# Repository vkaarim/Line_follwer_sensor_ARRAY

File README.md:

# 16-Channel IR Sensor Array PCB

> Personal hardware project for my robotics portfolio.

---

## Purpose

Design a custom 16-channel infrared sensor array PCB for future high-speed Line Follower robots.

This board will replace commercial sensor arrays and provide a platform for future improvements and experiments.

---

## Status

- [x] Schematic completed
- [x] PCB completed
- [x] 3D model verified
- [x] DRC passed
- [x] Gerber generated
- [x] Uploaded to GitHub

Version: **V1**

---

## Repository Structure

```
Hardware/
Images/
Manufacturing/
Backups/
README.md
```

---

## Images

### PCB Layout

### Schematic

### 3D Front

### 3D Back

---

## Main Specifications

- Software: KiCad
- Sensor Channels: 16
- PCB Type: 2 Layers
- Sensor Type: TCRT5000
- Target Robot: Line Follower

---

## Files Included

✔ KiCad Project

✔ Schematic

✔ PCB Layout

✔ Gerber Files

✔ 3D Images

✔ Backups

---

## Notes

Things I learned while designing this PCB:

- Organizing footprints before routing saves time.
- Keep signal routing clean and avoid unnecessary crossings.
- Always run DRC before generating Gerbers.
- Name files and folders consistently.
- Save manufacturing files separately from project files.

---

## Future Improvements

Version 2 ideas:

- Use SMD components where possible.
- Reduce PCB size.
- Improve sensor spacing.
- Add calibration LEDs.
- Add onboard multiplexer.
- Improve silkscreen readability.

---

## Manufacturing

Gerber files are available inside the repository.

---

## Author

Karim Rahou

National Higher School of Autonomous Systems

Personal learning project.

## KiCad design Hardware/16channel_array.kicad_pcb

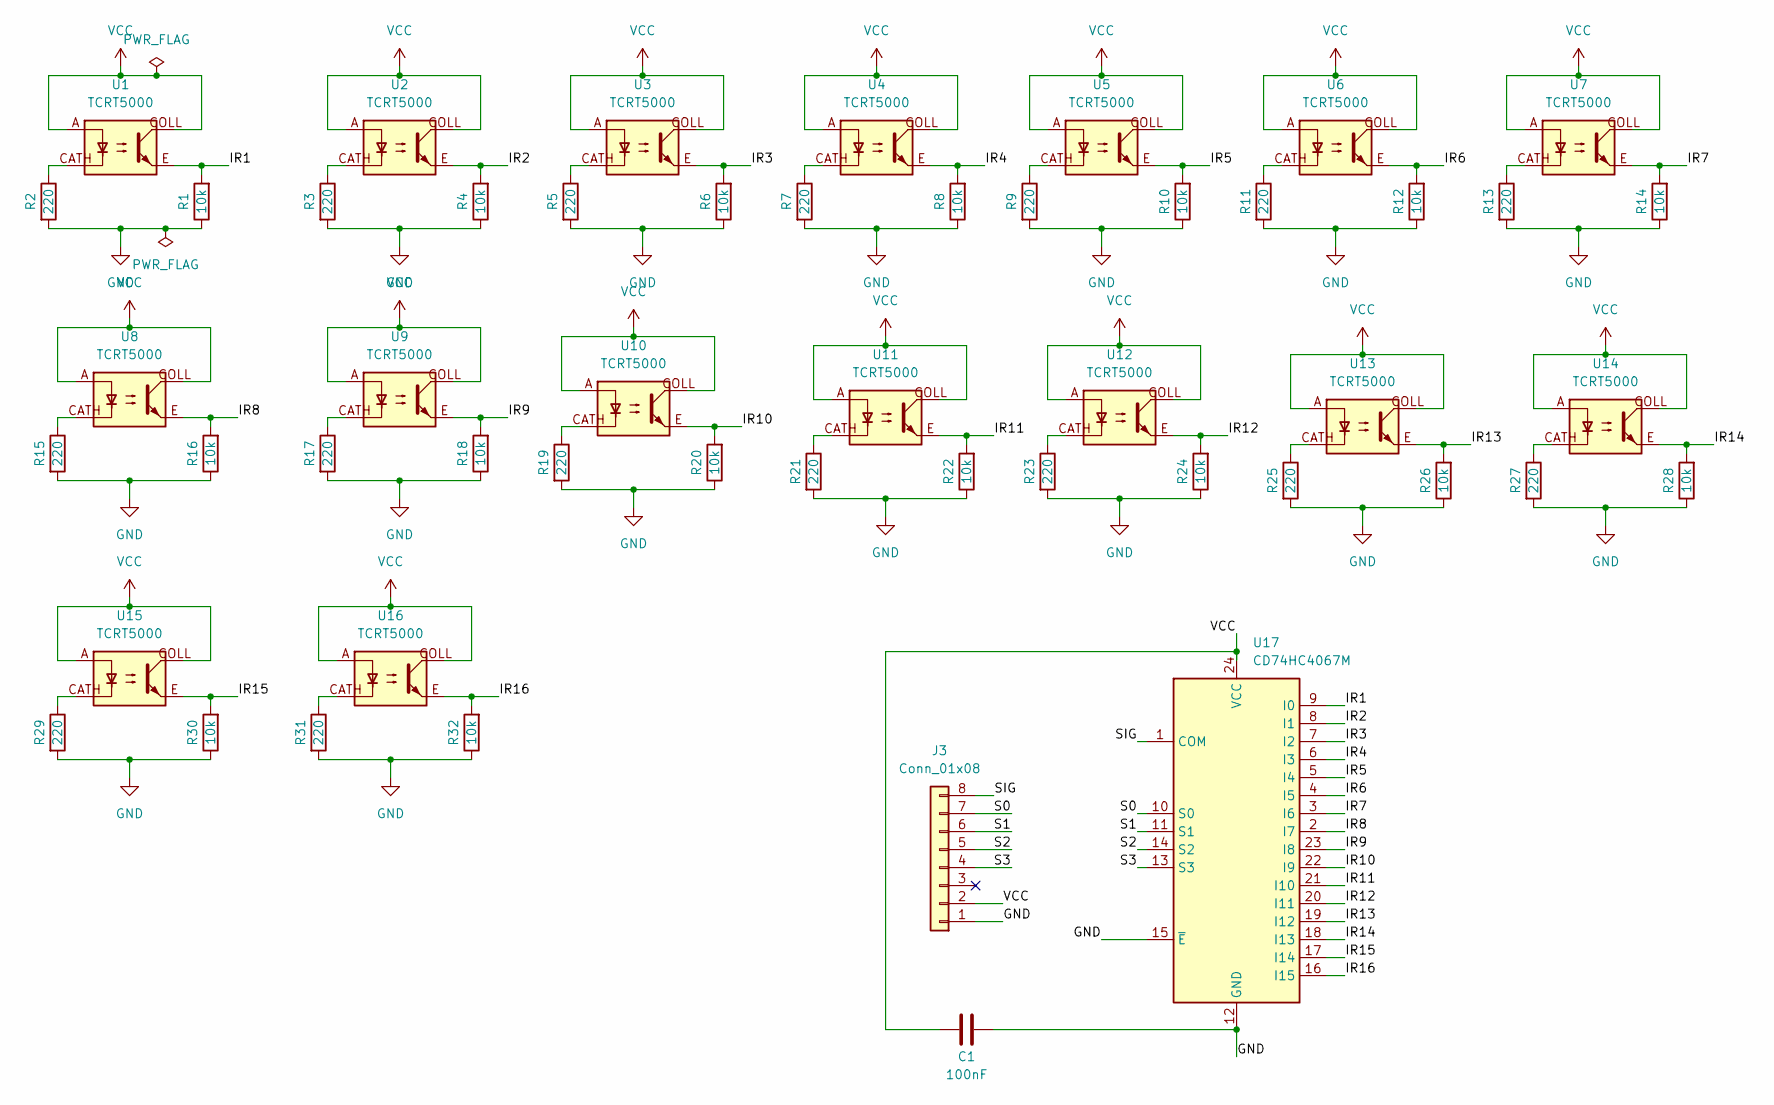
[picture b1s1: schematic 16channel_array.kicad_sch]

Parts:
C1: 100nF; C_0805_2012Metric
J3: Conn_01x08; PinHeader_1x08_P2.54mm_Vertical
R1, R4, R6, R8, R10, R12, R14, R16, R18, R20, R22, R24, R26, R28, R30, R32: 10k; R_0805_2012Metric
R2, R3, R5, R7, R9, R11, R13, R15, R17, R19, R21, R23, R25, R27, R29, R31: 220; R_0805_2012Metric
U1, U2, U3, U4, U5, U6, U7, U8, U9, U10, U11, U12, U13, U14, U15, U16: TCRT5000; tcrt5000
U17: CD74HC4067M; SOIC-24W_7.5x15.4mm_P1.27mm

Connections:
/IR1: R1.2, U1.E, U17.9 (I0)
/IR2: R4.2, U2.E, U17.8 (I1)
/IR3: R6.2, U3.E, U17.7 (I2)
/IR4: R8.2, U4.E, U17.6 (I3)
/IR5: R10.2, U5.E, U17.5 (I4)
/IR6: R12.2, U6.E, U17.4 (I5)
/IR7: R14.2, U7.E, U17.3 (I6)
/IR8: R16.2, U8.E, U17.2 (I7)
/IR9: R18.2, U9.E, U17.23 (I8)
/IR10: R20.2, U10.E, U17.22 (I9)
/IR11: R22.2, U11.E, U17.21 (I10)
/IR12: R24.2, U12.E, U17.20 (I11)
/IR13: R26.2, U13.E, U17.19 (I12)
/IR14: R28.2, U14.E, U17.18 (I13)
/IR15: R30.2, U15.E, U17.17 (I14)
/IR16: R32.2, U16.E, U17.16 (I15)
/S0: J3.7, U17.10 (S0)
/S1: J3.6, U17.11 (S1)
/S2: J3.5, U17.14 (S2)
/S3: J3.4, U17.13 (S3)
/SIG: J3.8, U17.1 (COM)
GND: C1.2, J3.1, R1.1, R2.2, R3.2, R4.1, R5.2, R6.1, R7.2, R8.1, R9.2, R10.1, R11.2, R12.1, R13.2, R14.1, R15.2, R16.1, R17.2, R18.1, R19.2, R20.1, R21.2, R22.1, R23.2, R24.1, R25.2, R26.1, R27.2, R28.1, R29.2, R30.1, R31.2, R32.1, U17.12 (GND), U17.15 (~E)
unnamed: R2.1, U1.CATH
unnamed: R3.1, U2.CATH
unnamed: R5.1, U3.CATH
unnamed: R7.1, U4.CATH
unnamed: R9.1, U5.CATH
unnamed: R11.1, U6.CATH
unnamed: R13.1, U7.CATH
unnamed: R15.1, U8.CATH
unnamed: R17.1, U9.CATH
unnamed: R19.1, U10.CATH
unnamed: R21.1, U11.CATH
unnamed: R23.1, U12.CATH
unnamed: R25.1, U13.CATH
unnamed: R27.1, U14.CATH
unnamed: R29.1, U15.CATH
unnamed: R31.1, U16.CATH
VCC: C1.1, J3.2, U1.A, U1.COLL, U2.A, U2.COLL, U3.A, U3.COLL, U4.A, U4.COLL, U5.A, U5.COLL, U6.A, U6.COLL, U7.A, U7.COLL, U8.A, U8.COLL, U9.A, U9.COLL, U10.A, U10.COLL, U11.A, U11.COLL, U12.A, U12.COLL, U13.A, U13.COLL, U14.A, U14.COLL, U15.A, U15.COLL, U16.A, U16.COLL, U17.24 (VCC)

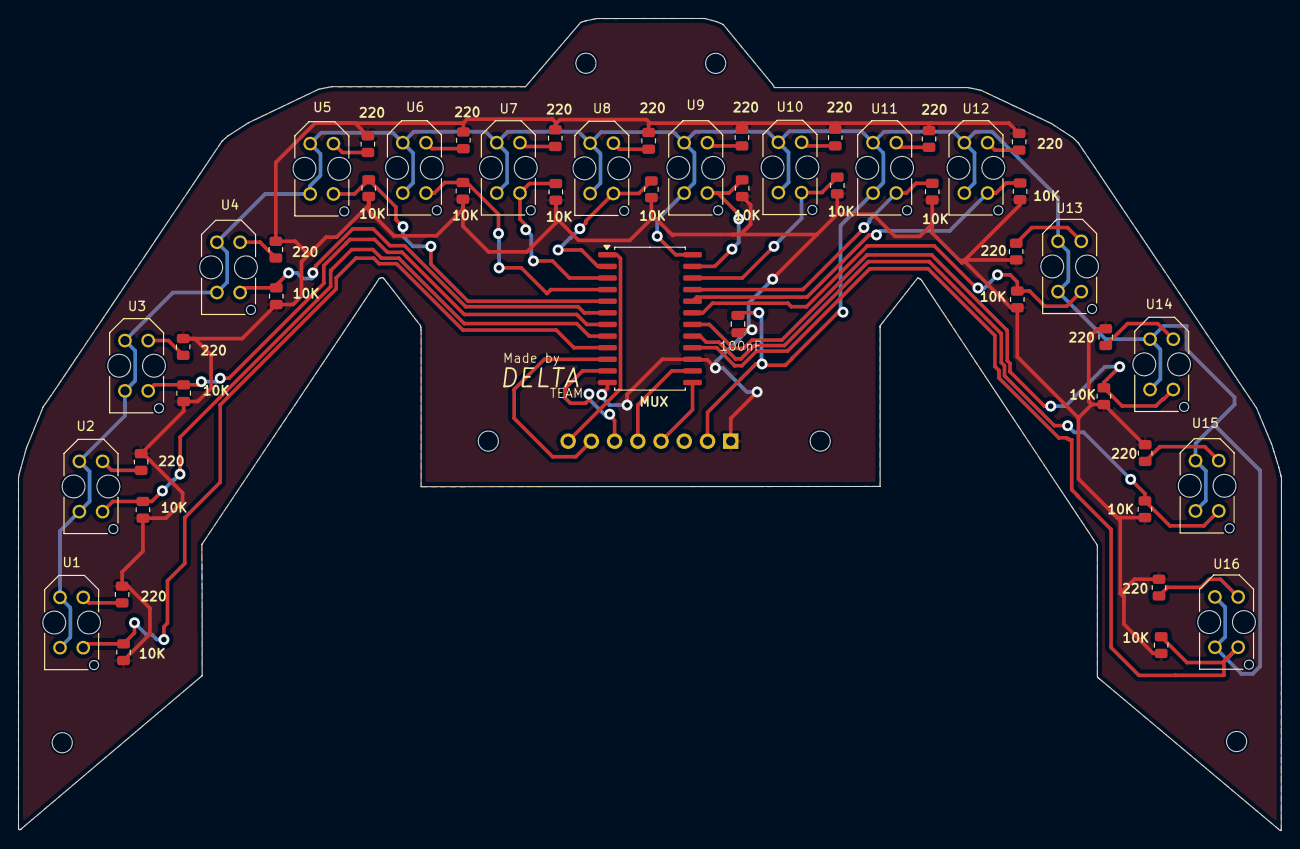
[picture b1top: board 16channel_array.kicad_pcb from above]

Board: 2 copper layers, 138.1 x 88.8 mm, 51 parts (1 on the bottom side), 39 nets.
